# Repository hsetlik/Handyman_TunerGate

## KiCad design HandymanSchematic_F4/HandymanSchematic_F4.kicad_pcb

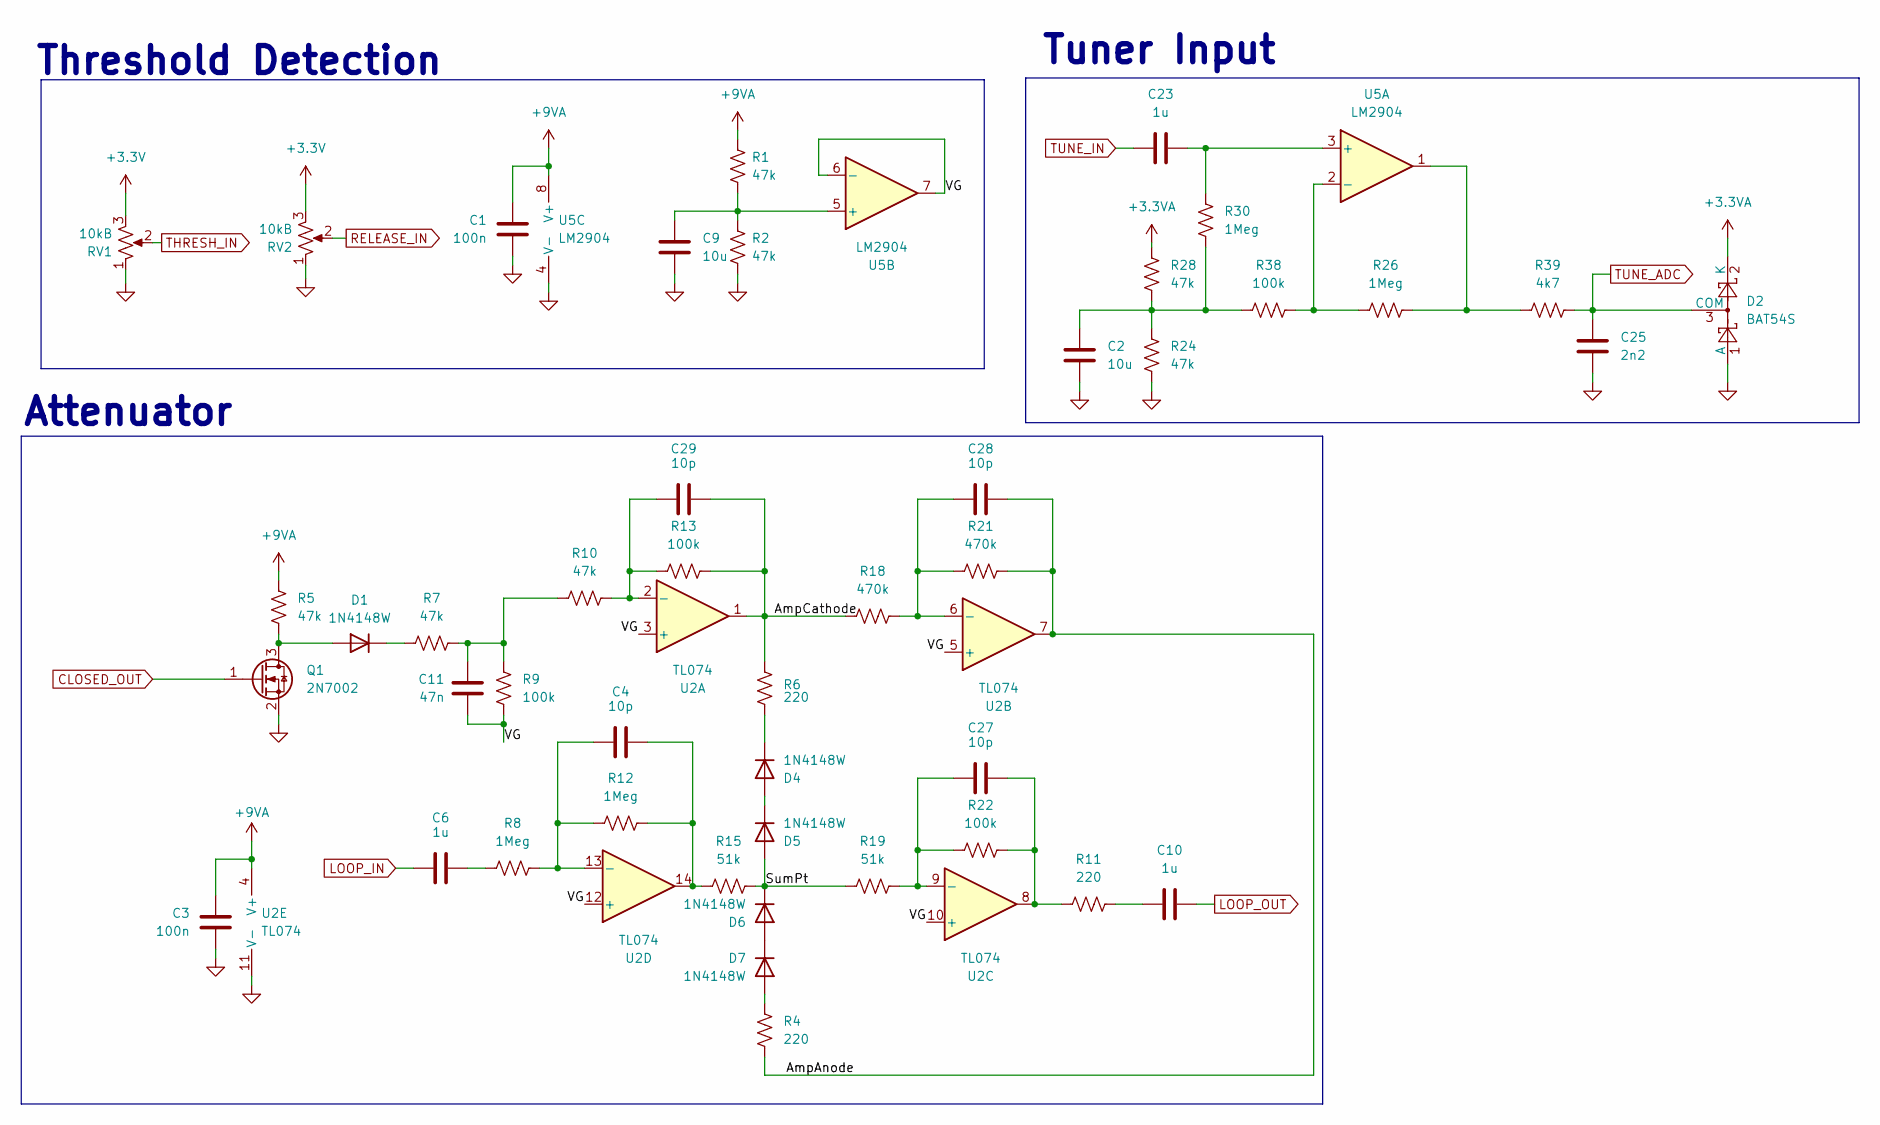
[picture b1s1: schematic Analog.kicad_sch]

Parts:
C1, C3: 100n; C_0805_2012Metric; MPN KGF21BR71H104KT
C2, C9: 10u; C_0805_2012Metric; MPN KGF21BR71H104KT
C4, C27, C28, C29: 10p; C_0805_2012Metric; MPN KGM21AR51E105KU
C6, C10, C23: 1u; C_0805_2012Metric; MPN KGM21AR51E105KU
C11: 47n; C_0805_2012Metric; MPN KGM21NR71H472JM
C25: 2n2; C_0805_2012Metric; MPN KGF21BR71H104KT
D1, D4, D5, D6, D7: 1N4148W; D_SOD-123; MPN 1N4148W-7-F
D2: BAT54S; SOT-23
Q1: 2N7002; SOT-23
R1, R2, R5, R7, R10, R24, R28: 47k; R_0805_2012Metric; MPN RK73B2ATTE473J
R4, R6, R11: 220; R_0805_2012Metric; MPN RC0805FR-10100KL
R8, R12, R26: 1Meg; R_0805_2012Metric; MPN AC0805JR-07470KL
R9, R22: 100k; R_0805_2012Metric; MPN RC0805FR-10100KL
R13, R38: 100k; R_0805_2012Metric; MPN AC0805JR-07470KL
R15, R19: 51k; R_0805_2012Metric; MPN RT0805FRE0751KL
R18, R21: 470k; R_0805_2012Metric; MPN AC0805JR-07470KL
R30: 1Meg; R_0805_2012Metric; MPN RK73B2ATTE473J
R39: 4k7; R_0805_2012Metric; MPN AC0805JR-07470KL
RV1, RV2: 10kB; Potentiometer_Alpha_RD901F-40-00D_Single_Vertical_CircularH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; MPN RV9022NO-PA30B7.0-B10K-000-W3.0
U2: TL074; SOIC-14_3.9x8.7mm_P1.27mm; MPN TL074HIDR
U5: LM2904; SOIC-8_3.9x4.9mm_P1.27mm

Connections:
+3.3V: RV1.3, RV2.3; also elsewhere on the board
+3.3VA: D2.2 (K), R28.1; also elsewhere on the board
+9VA: C1.1, C3.1, R1.1, R5.1, U2.4 (V+), U5.8 (V+); also elsewhere on the board
/Analog/AmpAnode: C28.2, R4.2, R21.2, U2.7
/Analog/AmpCathode: C29.2, R6.1, R13.2, R18.1, U2.1
/Analog/SumPt: D5.2 (A), D6.1 (K), R15.2, R19.1
/Analog/VG: C11.2, R9.2, U2.3 (+), U2.5 (+), U2.10 (+), U2.12 (+), U5.6 (-), U5.7
CLOSED_OUT: Q1.1 (G); also elsewhere on the board
GND: C1.2, C2.2, C3.2, C9.2, C25.2, D2.1 (A), Q1.2 (S), R2.2, R24.2, RV1.1, RV2.1, U2.11 (V-), U5.4 (V-); also elsewhere on the board
LOOP_IN: C6.1; also elsewhere on the board
LOOP_OUT: C10.2; also elsewhere on the board
unnamed: C2.1, R24.1, R28.2, R30.2, R38.1
unnamed: C4.2, R12.2, R15.1, U2.14
unnamed: C6.2, R8.1
unnamed: C10.1, R11.2
unnamed: C11.1, R7.2, R9.1, R10.1
unnamed: C27.2, R11.1, R22.2, U2.8
unnamed: D1.2 (A), Q1.3 (D), R5.2
unnamed: D1.1 (K), R7.1
unnamed: D4.2 (A), D5.1 (K)
unnamed: D4.1 (K), R6.2
unnamed: D6.2 (A), D7.1 (K)
unnamed: D7.2 (A), R4.1
unnamed: R26.2, R39.1, U5.1
unnamed: C29.1, R10.2, R13.1, U2.2 (-)
unnamed: C28.1, R18.2, R21.1, U2.6 (-)
unnamed: C27.1, R19.2, R22.1, U2.9 (-)
unnamed: C4.1, R8.2, R12.1, U2.13 (-)
unnamed: C23.2, R30.1, U5.3 (+)
unnamed: R26.1, R38.2, U5.2 (-)
unnamed: C9.1, R1.2, R2.1, U5.5 (+)
RELEASE_IN: RV2.2; also elsewhere on the board
THRESH_IN: RV1.2; also elsewhere on the board
TUNE_ADC: C25.1, D2.3 (COM), R39.2; also elsewhere on the board
TUNE_IN: C23.1; also elsewhere on the board

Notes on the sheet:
Threshold Detection
Tuner Input
Attenuator

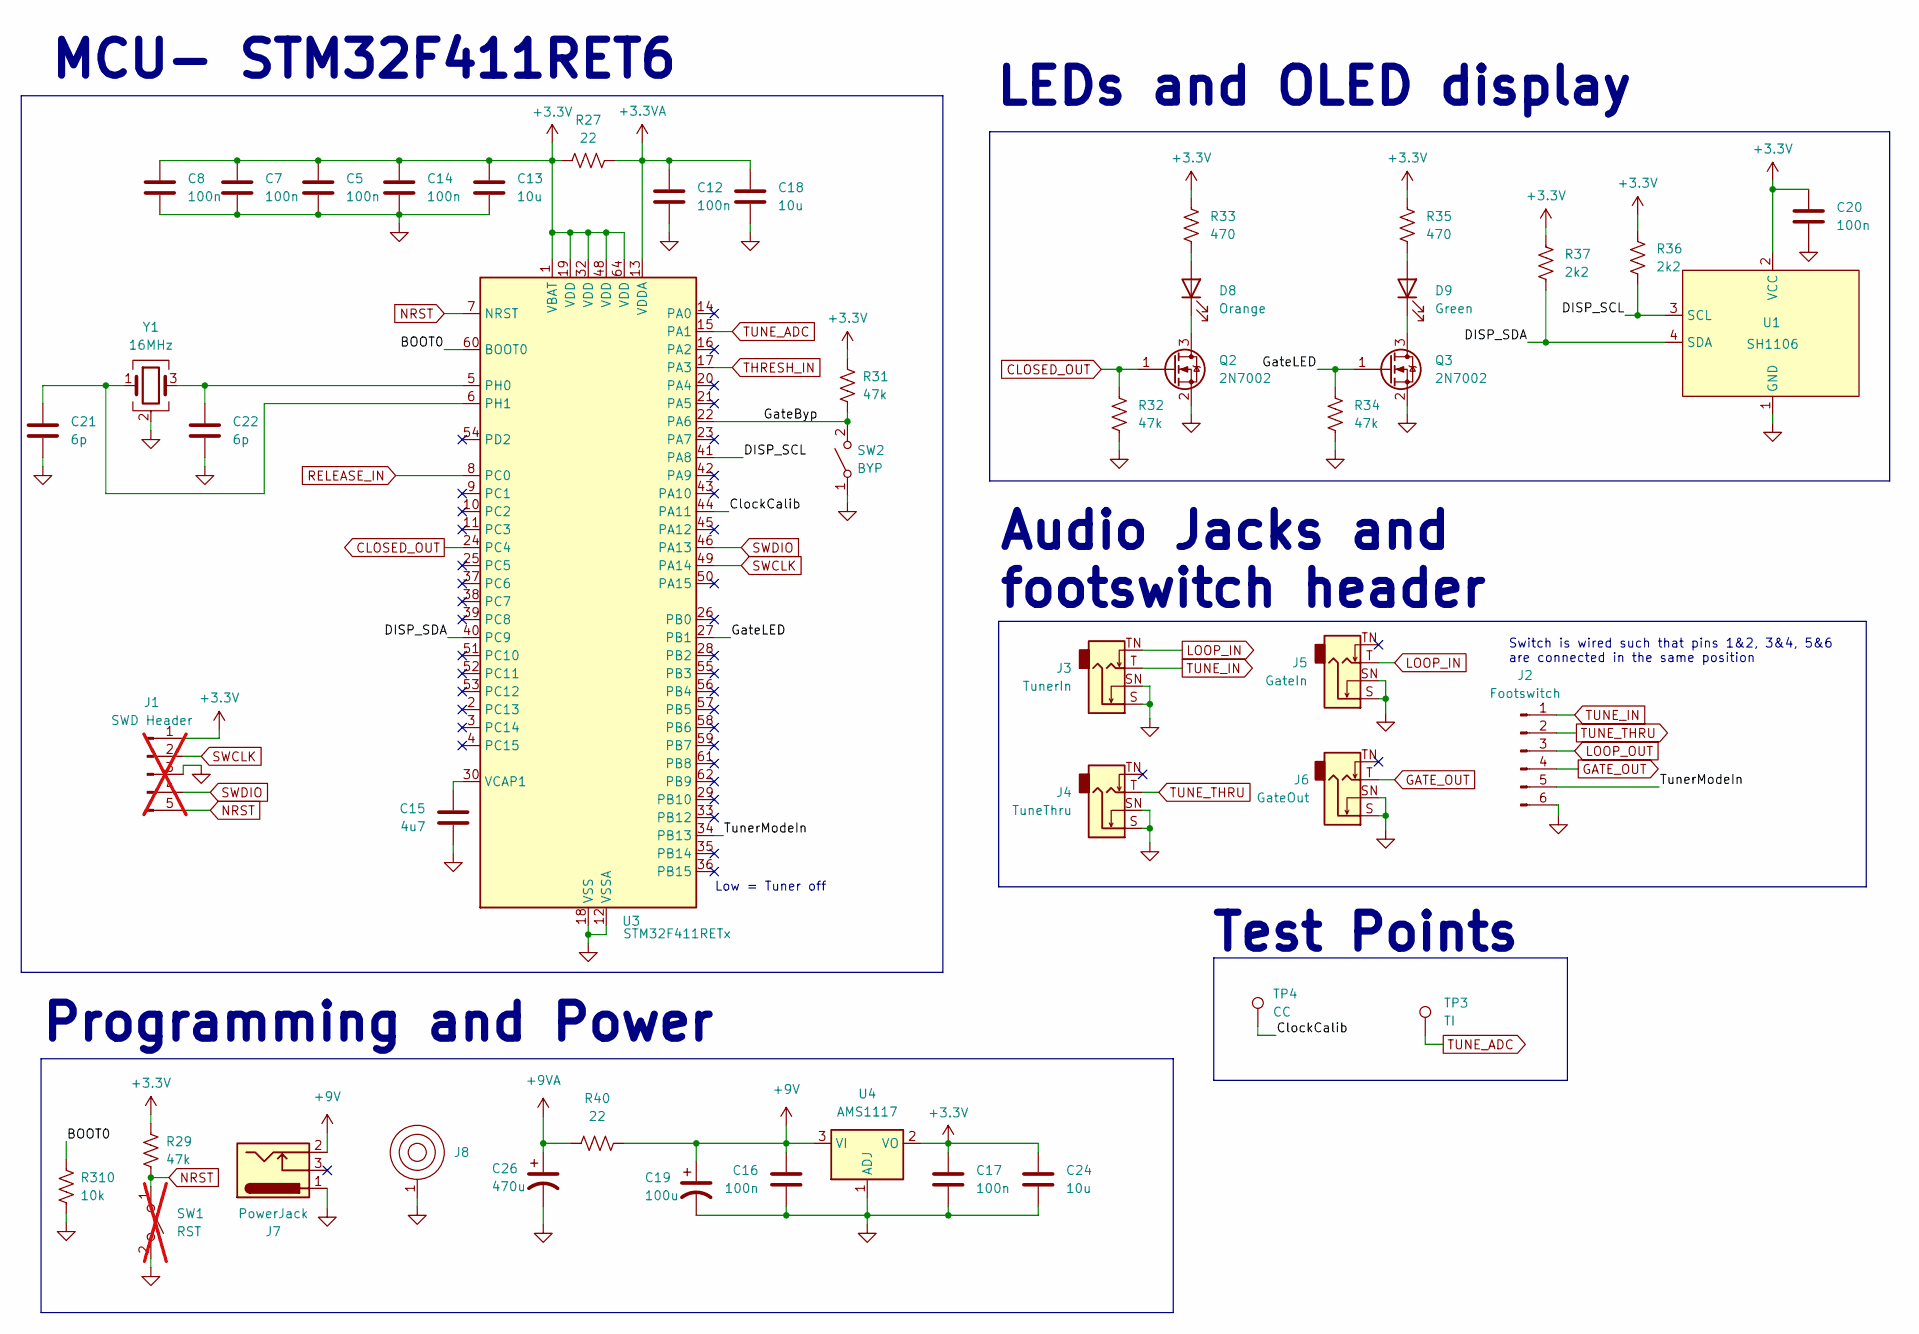
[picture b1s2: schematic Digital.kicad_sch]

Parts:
C5, C7, C8, C12, C14, C16, C17, C20: 100n; C_0805_2012Metric; MPN KGF21BR71H104KT
C13, C18, C24: 10u; C_0805_2012Metric; MPN KGM21AR50J106KU
C15: 4u7; C_0805_2012Metric; MPN CGA4J3X7R1A475K125AB
C19: 100u; CP_Radial_D5.0mm_P2.50mm; MPN ESH107M010AC3AA
C21, C22: 6p; C_0805_2012Metric; MPN 0805N6R0D500CT
C26: 470u; CP_Radial_D6.3mm_P2.50mm; MPN ESH107M010AC3AA
D8: Orange; LED_D3.0mm; MPN LTL-4291N
D9: Green; LED_D3.0mm; MPN LTL-4231N
J1: SWD Header; PinHeader_1x05_P2.54mm_Vertical; not fitted
J2: Footswitch; PinHeader_1x06_P2.54mm_Vertical; MPN SF17N-0302-21R-L-1.1KG-R
J3: TunerIn; Jack_6.35mm_Tayda_PJ664C_Mono_Horizontal; MPN PJ-644C MONO
J4: TuneThru; Jack_6.35mm_Tayda_PJ664C_Mono_Horizontal; MPN PJ-644C MONO
J5: GateIn; Jack_6.35mm_Tayda_PJ664C_Mono_Horizontal; MPN PJ-644C MONO
J6: GateOut; Jack_6.35mm_Tayda_PJ664C_Mono_Horizontal; MPN PJ-644C MONO
J7: PowerJack; BarrelJack_Horizontal; MPN NEB 21 R-C
J8: BatteryContact_Keystone_243
Q2, Q3: 2N7002; SOT-23; MPN 2N7002NXAKR
R27: 22; R_0805_2012Metric; MPN RC0805JR-0722RL
R29, R31, R32, R34: 47k; R_0805_2012Metric; MPN RK73B2ATTE473J
R33, R35: 470; R_0805_2012Metric; MPN RC0805JR-10470RL
R36, R37: 2k2; R_0805_2012Metric; MPN AC0805FR-072K2L
R40: 22; R_0805_2012Metric; MPN RC0805JR-10470RL
R310: 10k; R_0805_2012Metric; MPN AC0805JR-0710KL
SW1: RST; SW_SPST_B3U-1000P; not fitted
SW2: BYP; SW_TH_Tactile_Omron_B3F-102x; MPN TS02-66-90-BK-100-SCR-D
TP3: TI; TestPoint_THTPad_D2.0mm_Drill1.0mm_VAL
TP4: CC; TestPoint_THTPad_D2.0mm_Drill1.0mm_VAL
U1: SH1106; OLED_SH1106_13_OffBoard; MPN SH1106
U3: STM32F411RETx; LQFP-64_10x10mm_P0.5mm; MPN STM32F411RET6TR
U4: AMS1117; SOT-223-3_TabPin2; MPN LD1117S33CTR
Y1: 16MHz; Crystal_SMD_3225-4Pin_3.2x2.5mm; MPN CX3225FB16000B0FZZH1

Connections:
+3.3V: C5.2, C7.2, C8.2, C13.2, C14.2, C17.2, C20.2, C24.2, J1.1, R27.1, R29.1, R31.1, R33.1, R35.1, R36.1, R37.1, U1.2 (VCC), U3.1 (VBAT), U3.19 (VDD), U3.32 (VDD), U3.48 (VDD), U3.64 (VDD), U4.2 (VO); also elsewhere on the board
+3.3VA: C12.2, C18.2, R27.2, U3.13 (VDDA); also elsewhere on the board
+9V: C16.2, C19.1, J7.2, R40.2, U4.3 (VI)
+9VA: C26.1, R40.1; also elsewhere on the board
/Digital/BOOT0: R310.1, U3.60 (BOOT0)
/Digital/ClockCalib: TP4.1 (1_1), U3.44 (PA11)
/Digital/DISP_SCL: R36.2, U1.3 (SCL), U3.41 (PA8)
/Digital/DISP_SDA: R37.2, U1.4 (SDA), U3.40 (PC9)
/Digital/GateByp: R31.2, SW2.2 (B), U3.22 (PA6)
/Digital/GateLED: Q3.1 (G), R34.2, U3.27 (PB1)
/Digital/TunerModeIn: J2.5, U3.34 (PB13)
CLOSED_OUT: Q2.1 (G), R32.2, U3.24 (PC4); also elsewhere on the board
GATE_OUT: J2.4, J6.T
GND: C5.1, C7.1, C8.1, C12.1, C13.1, C14.1, C15.1, C16.1, C17.1, C18.1, C19.2, C20.1, C21.1, C22.1, C24.1, C26.2, J1.3, J2.6, J3.S, J3.SN, J4.S, J4.SN, J5.S, J5.SN, J6.S, J6.SN, J7.1, J8.1, Q2.2 (S), Q3.2 (S), R32.1, R34.1, R310.2, SW1.2 (B), SW2.1 (A), U1.1 (GND), U3.12 (VSSA), U3.18 (VSS), U3.31 (VSS), U3.47 (VSS), U3.63 (VSS), U4.1 (ADJ), Y1.2 (G), Y1.4 (G); also elsewhere on the board
LOOP_IN: J3.TN, J5.T; also elsewhere on the board
LOOP_OUT: J2.3; also elsewhere on the board
NRST: J1.5, R29.2, SW1.1 (A), U3.7 (NRST)
unnamed: D8.2 (A), R33.2
unnamed: D8.1 (K), Q2.3 (D)
unnamed: D9.2 (A), R35.2
unnamed: D9.1 (K), Q3.3 (D)
unnamed: C22.2, U3.5 (PH0), Y1.3
unnamed: C21.2, U3.6 (PH1), Y1.1
unnamed: C15.2, U3.30 (VCAP1)
RELEASE_IN: U3.8 (PC0); also elsewhere on the board
SWCLK: J1.2, U3.49 (PA14)
SWDIO: J1.4, U3.46 (PA13)
THRESH_IN: U3.17 (PA3); also elsewhere on the board
TUNE_ADC: TP3.1 (1_1), U3.15 (PA1); also elsewhere on the board
TUNE_IN: J2.1, J3.T; also elsewhere on the board
TUNE_THRU: J2.2, J4.T

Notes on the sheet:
LEDs and OLED display
Programming and Power
Audio Jacks and footswitch header
Switch is wired such that pins 1&2, 3&4, 5&6 are connected in the same position
Low = Tuner off
MCU- STM32F411RET6
Test Points

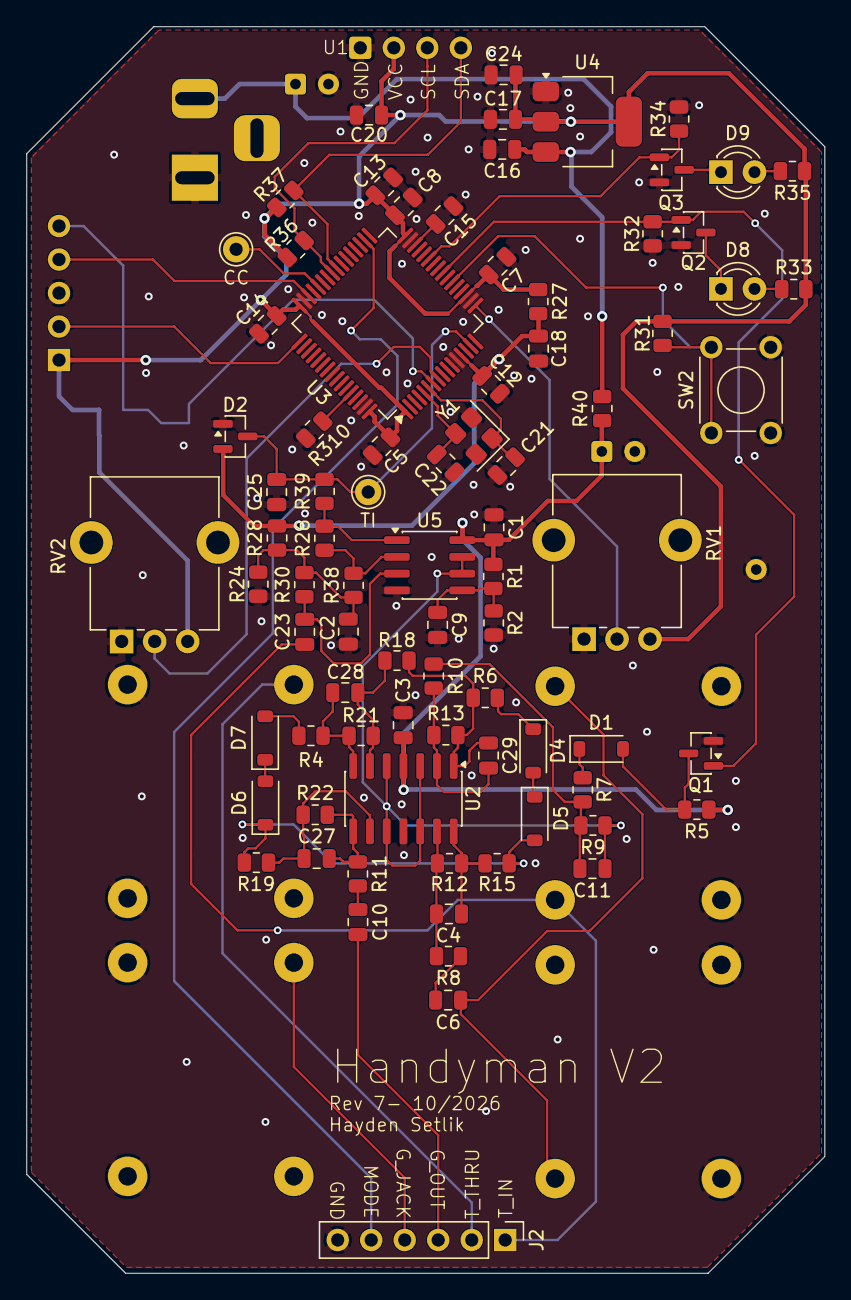
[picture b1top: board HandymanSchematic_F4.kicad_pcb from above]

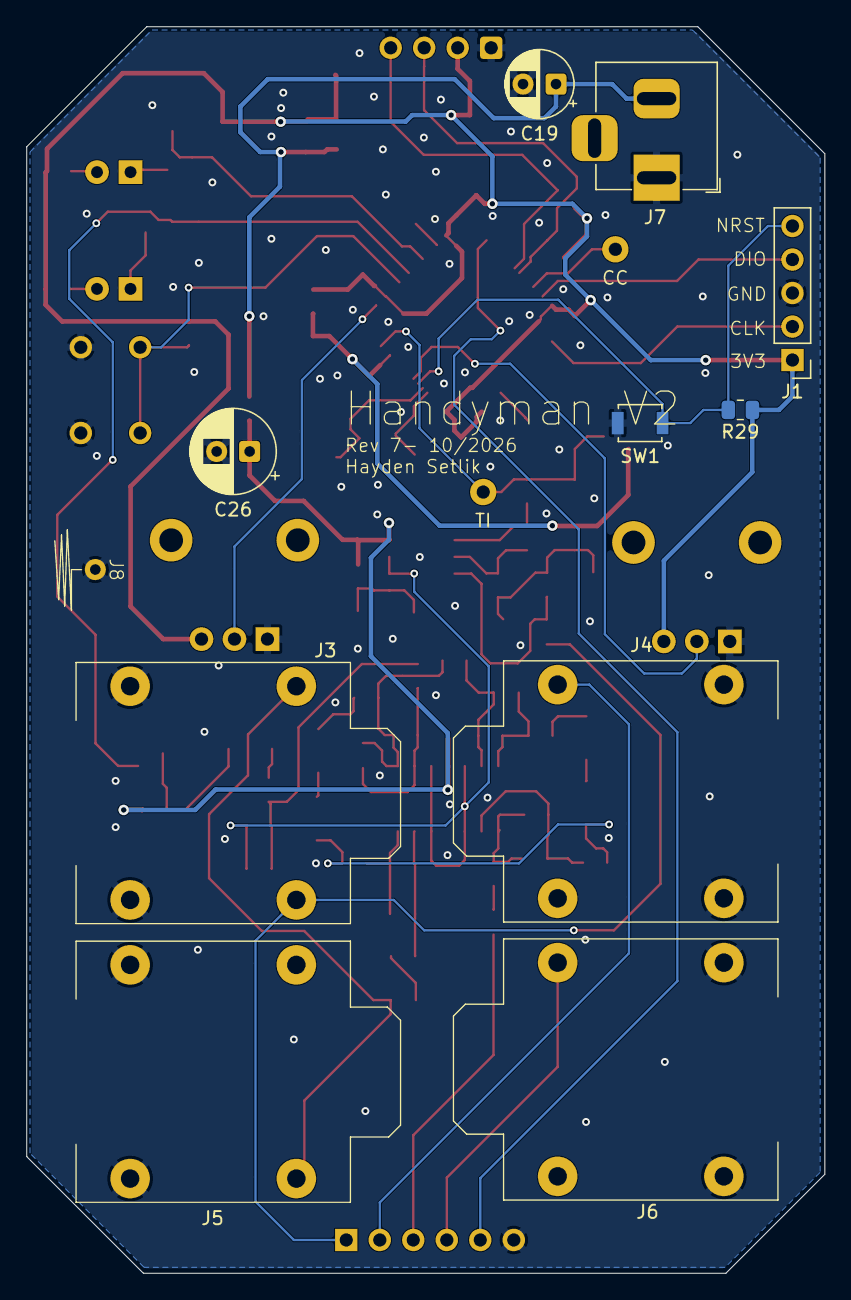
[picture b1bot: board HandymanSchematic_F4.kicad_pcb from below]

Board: 4 copper layers, 60.5 x 94.5 mm, 94 parts (11 on the bottom side), 55 nets.

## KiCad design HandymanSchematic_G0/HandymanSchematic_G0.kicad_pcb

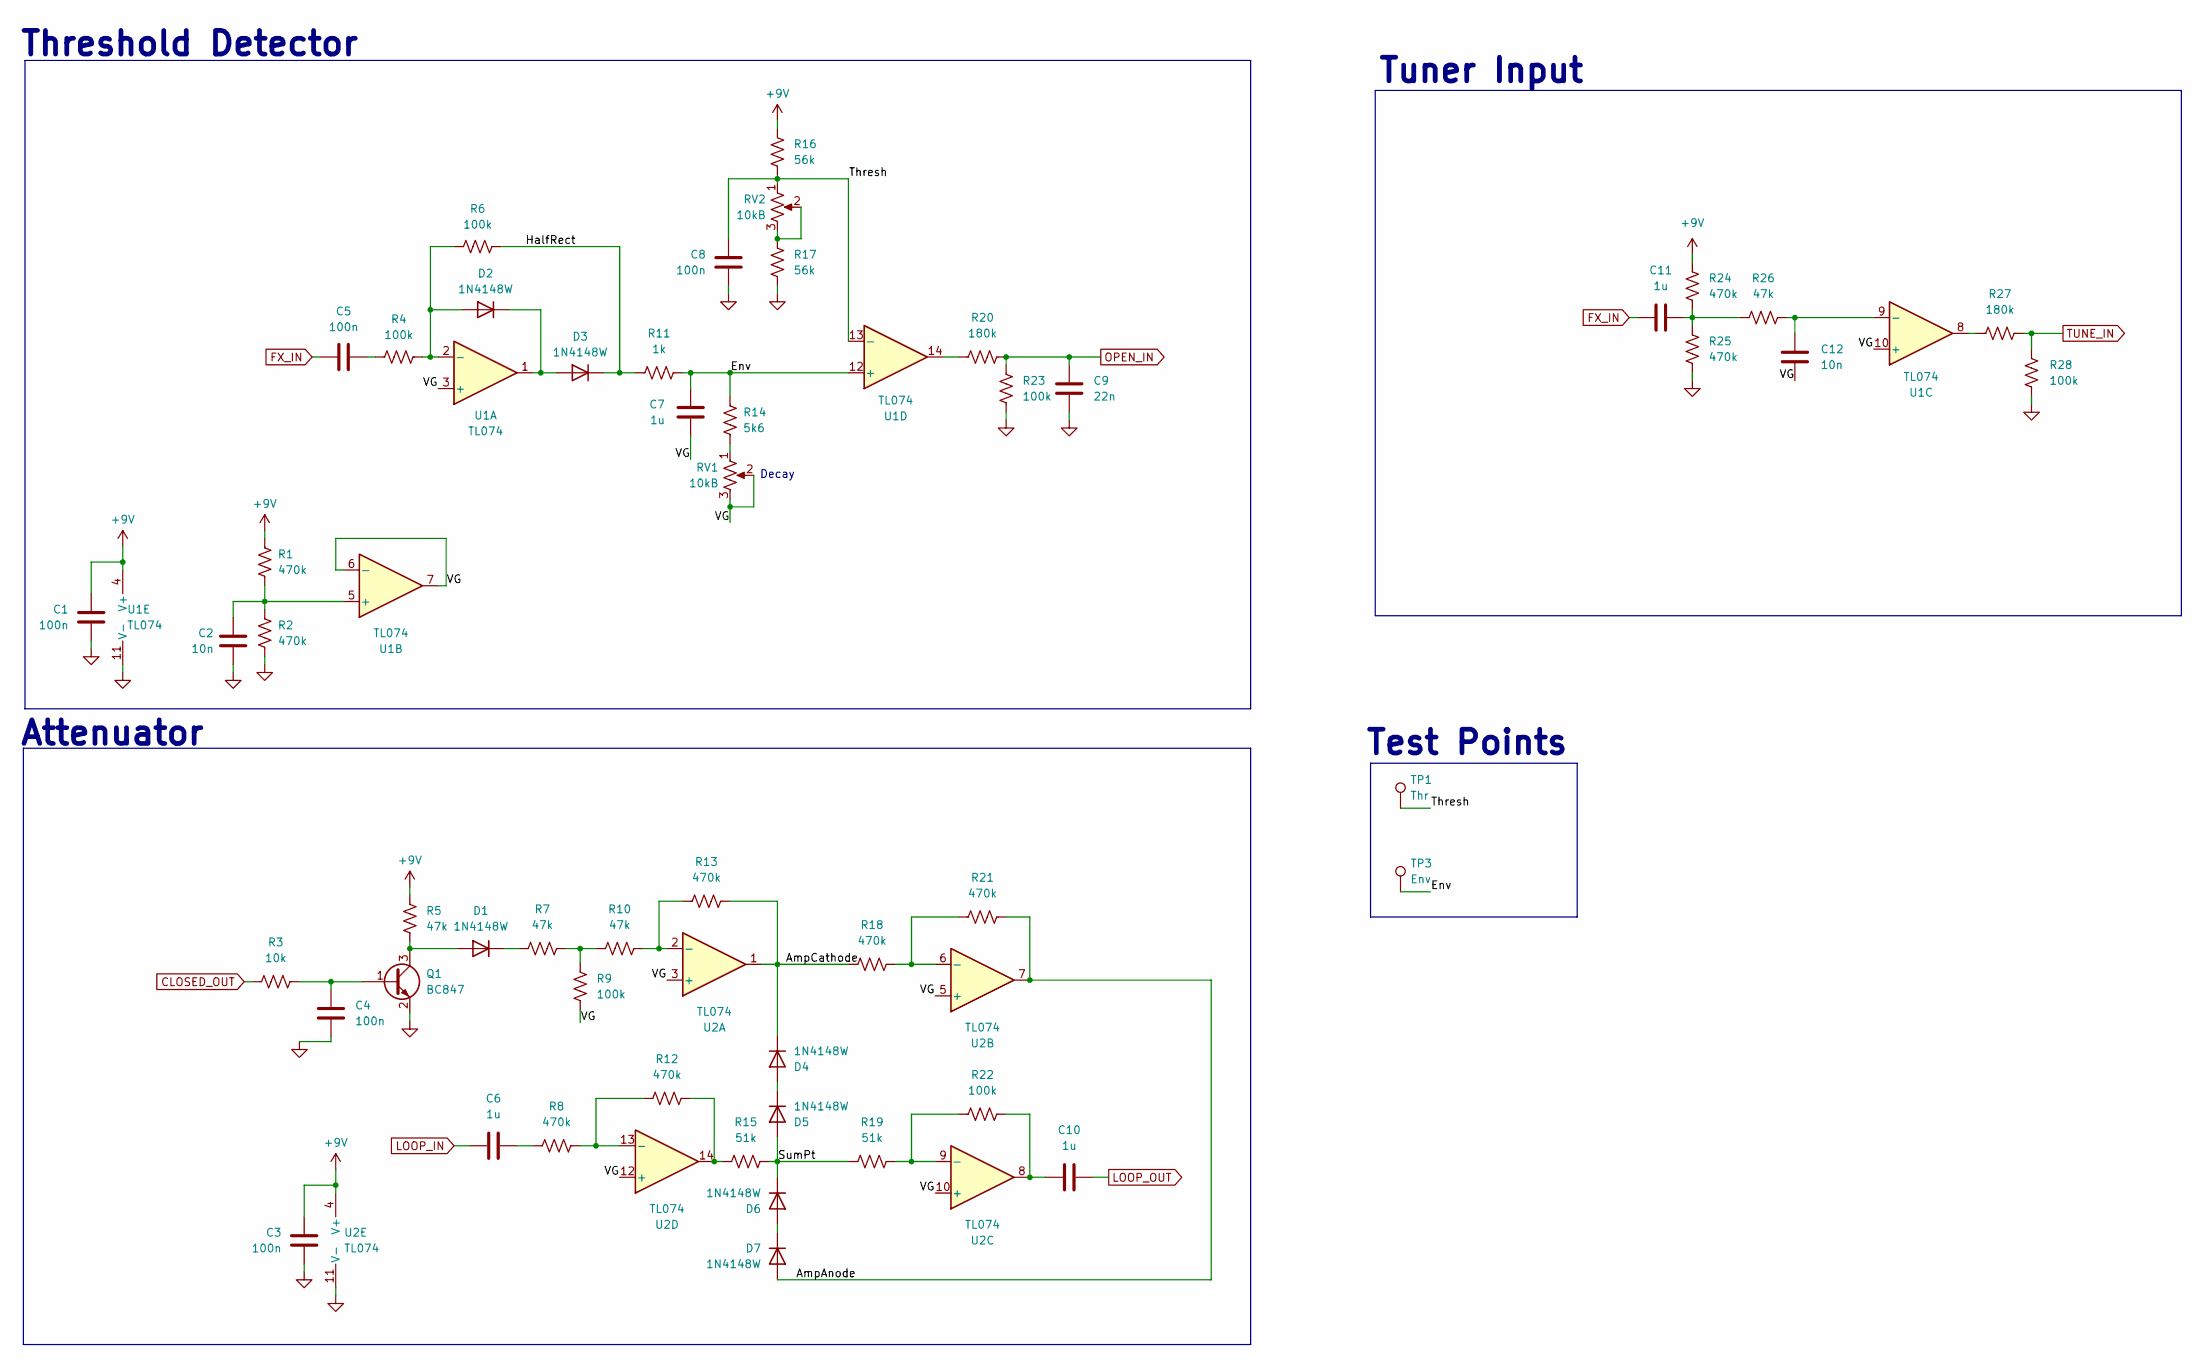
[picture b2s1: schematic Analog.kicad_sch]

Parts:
C1, C3, C4, C5, C8: 100n; C_0805_2012Metric
C2, C12: 10n; C_0805_2012Metric
C6, C7, C10, C11: 1u; C_0805_2012Metric
C9: 22n; C_0805_2012Metric
D1, D2, D3, D4, D5, D6, D7: 1N4148W; D_SOD-123
Q1: BC847; SOT-23
R1, R2, R8, R12, R13, R18, R21, R24, R25: 470k; R_0805_2012Metric
R3: 10k; R_0805_2012Metric
R4, R6, R9, R22, R23, R28: 100k; R_0805_2012Metric
R5, R7, R10, R26: 47k; R_0805_2012Metric
R11: 1k; R_0805_2012Metric
R14: 5k6; R_0805_2012Metric
R15, R19: 51k; R_0805_2012Metric
R16, R17: 56k; R_0805_2012Metric
R20, R27: 180k; R_0805_2012Metric
RV1, RV2: 10kB; Potentiometer_Alpha_RV16AF_42_Single_Long
TP1: Thr; TestPoint_THTPad_D2.0mm_Drill1.0mm_VAL
TP3: Env; TestPoint_THTPad_D2.0mm_Drill1.0mm_VAL
U1, U2: TL074; SOIC-14_3.9x8.7mm_P1.27mm

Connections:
+9V: C1.1, C3.1, R1.1, R5.1, R16.1, R24.2, U1.4 (V+), U2.4 (V+); also elsewhere on the board
/Analog/AmpAnode: D7.2 (A), R21.2, U2.7
/Analog/AmpCathode: D4.1 (K), R13.2, R18.1, U2.1
/Analog/Env: C7.1, R11.2, R14.1, TP3.1, U1.12 (+)
/Analog/HalfRect: D3.1 (K), R6.2, R11.1
/Analog/SumPt: D5.2 (A), D6.1 (K), R15.2, R19.1
/Analog/Thresh: C8.1, R16.2, RV2.1, TP1.1, U1.13 (-)
/Analog/VG: C7.2, C12.1, R9.2, RV1.2, RV1.3, U1.3 (+), U1.6 (-), U1.7, U1.10 (+), U2.3 (+), U2.5 (+), U2.10 (+), U2.12 (+)
CLOSED_OUT: R3.1; also elsewhere on the board
GND: C1.2, C2.2, C3.2, C4.2, C8.2, C9.2, Q1.2 (E), R2.2, R17.2, R23.2, R25.1, R28.1, U1.11 (V-), U2.11 (V-); also elsewhere on the board
LOOP_IN: C6.1; also elsewhere on the board
LOOP_OUT: C10.2; also elsewhere on the board
unnamed: C5.2, R4.1
unnamed: C6.2, R8.1
unnamed: C10.1, R22.2, U2.8
unnamed: C11.2, R24.1, R25.2, R26.1
unnamed: D1.2 (A), Q1.3 (C), R5.2
unnamed: D1.1 (K), R7.1
unnamed: D2.2 (A), R4.2, R6.1, U1.2 (-)
unnamed: D2.1 (K), D3.2 (A), U1.1
unnamed: D4.2 (A), D5.1 (K)
unnamed: D6.2 (A), D7.1 (K)
unnamed: C4.1, Q1.1 (B), R3.2
unnamed: R7.2, R9.1, R10.1
unnamed: R12.2, R15.1, U2.14
unnamed: R14.2, RV1.1
unnamed: R17.1, RV2.2, RV2.3
unnamed: R20.1, U1.14
unnamed: R27.1, U1.8
unnamed: C2.1, R1.2, R2.1, U1.5 (+)
unnamed: C12.2, R26.2, U1.9 (-)
unnamed: R10.2, R13.1, U2.2 (-)
unnamed: R18.2, R21.1, U2.6 (-)
unnamed: R19.2, R22.1, U2.9 (-)
unnamed: R8.2, R12.1, U2.13 (-)
OPEN_IN: C9.1, R20.2, R23.1; also elsewhere on the board
TUNE_IN: R27.2, R28.2; also elsewhere on the board

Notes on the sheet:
Threshold Detector
Tuner Input
Attenuator
Decay
Test Points

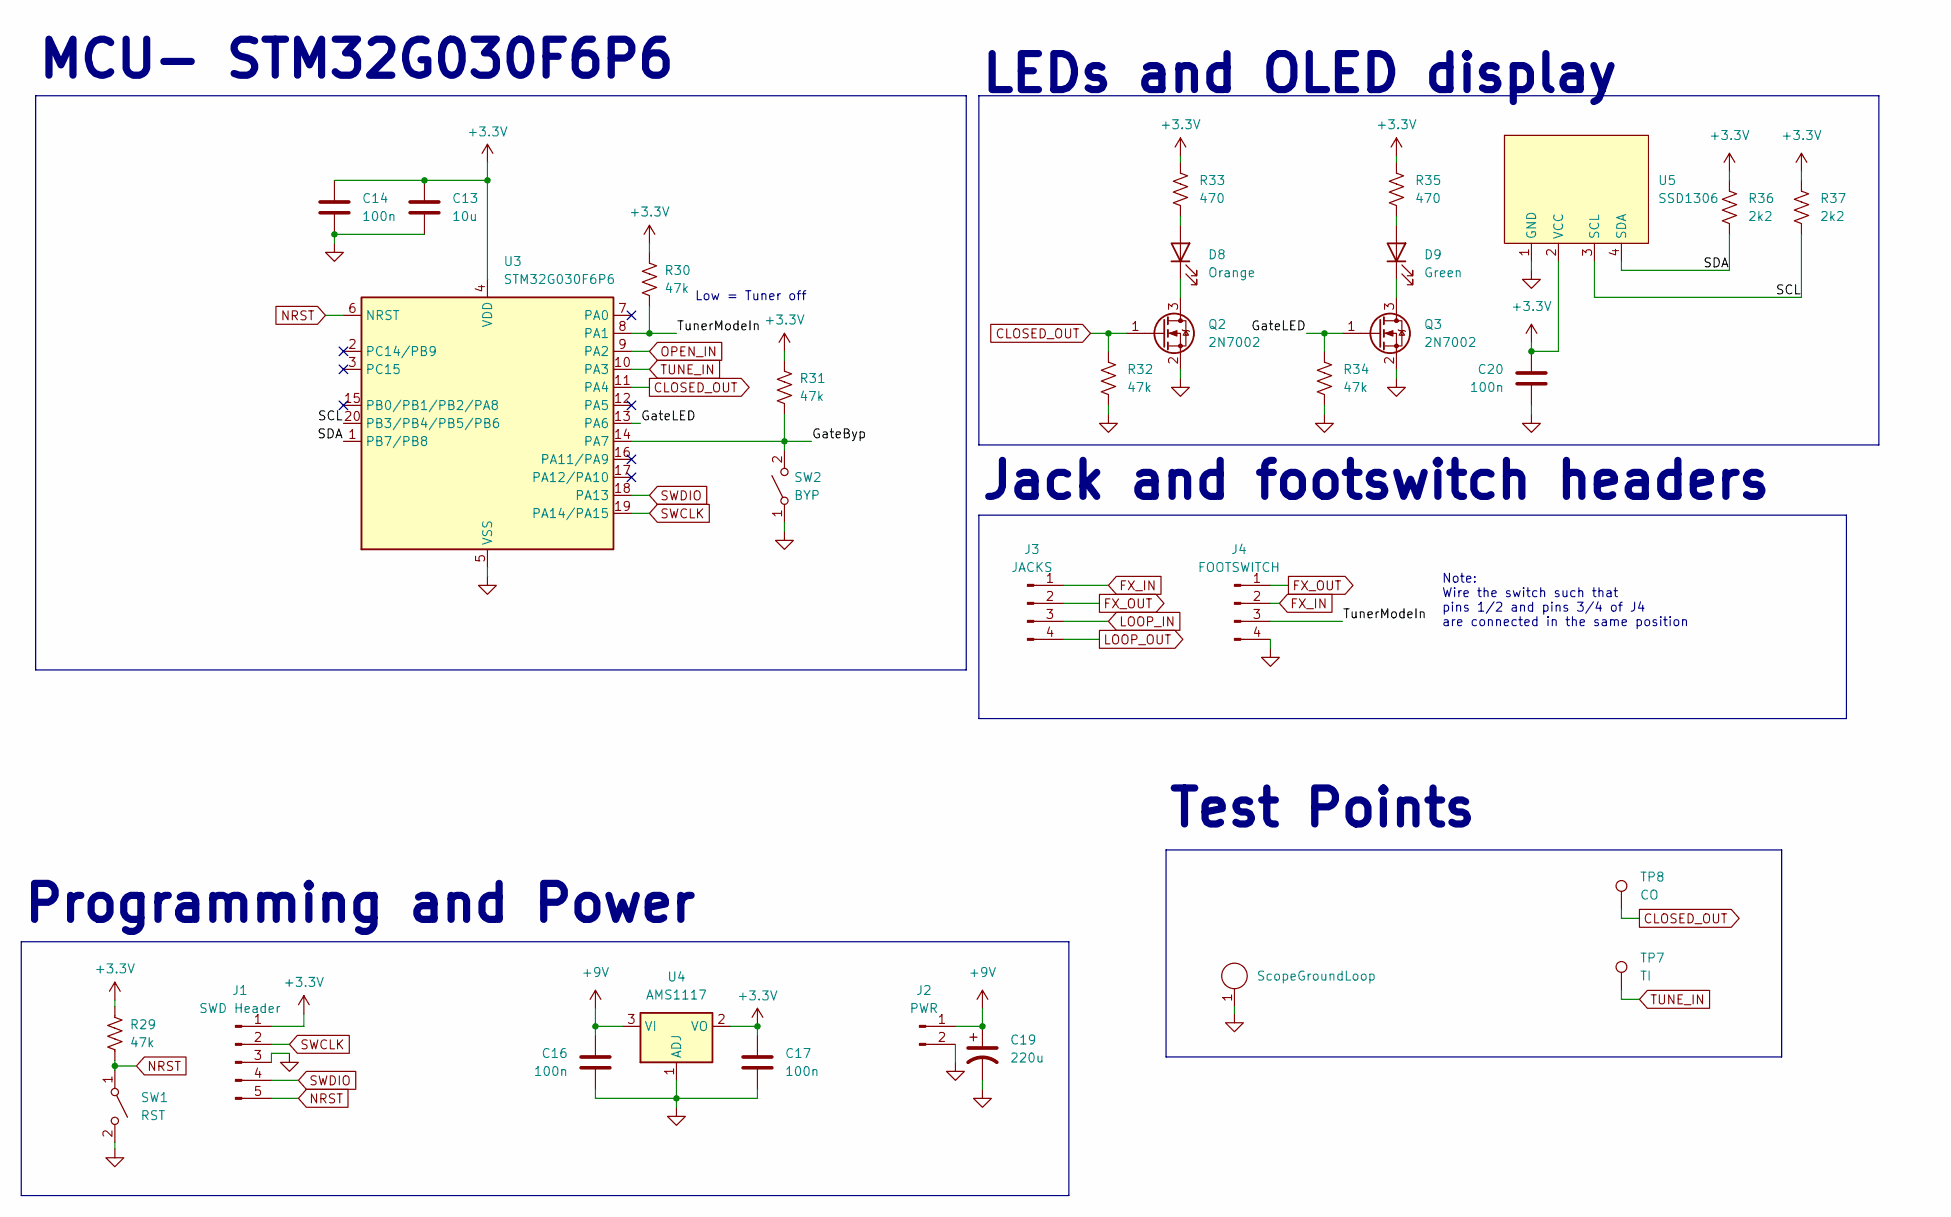
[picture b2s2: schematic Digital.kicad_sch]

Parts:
C13: 10u; C_0805_2012Metric
C14, C16, C17, C20: 100n; C_0805_2012Metric
C19: 220u; CP_Radial_D5.0mm_P2.50mm
D8: Orange; LED_D3.0mm
D9: Green; LED_D3.0mm
J1: SWD Header; PinHeader_1x05_P2.54mm_Vertical
J2: PWR; PinHeader_1x02_P2.54mm_Vertical
J3: JACKS; PinHeader_1x04_P2.54mm_Vertical
J4: FOOTSWITCH; PinHeader_1x04_P2.54mm_Vertical
J5: ScopeGroundLoop; THT_GND_WIRE
Q2, Q3: 2N7002; SOT-23
R29, R30, R31, R32, R34: 47k; R_0805_2012Metric
R33, R35: 470; R_0805_2012Metric
R36, R37: 2k2; R_0805_2012Metric
SW1: RST; SW_SPST_B3U-1000P
SW2: BYP; MiniToggle_SPST
TP7: TI; TestPoint_THTPad_D2.0mm_Drill1.0mm_VAL
TP8: CO; TestPoint_THTPad_D2.0mm_Drill1.0mm_VAL
U3: STM32G030F6P6; TSSOP-20_4.4x6.5mm_P0.65mm
U4: AMS1117; SOT-223-3_TabPin2
U5: SSD1306; SSD1306_OLED_128x64_OffBoard

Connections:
+3.3V: C13.2, C14.2, C17.2, C20.2, J1.1, R29.1, R30.1, R31.1, R33.1, R35.1, R36.1, R37.1, U3.4 (VDD), U4.2 (VO), U5.2 (VCC)
+9V: C16.2, C19.1, J2.1, U4.3 (VI); also elsewhere on the board
/Digital/GateByp: R31.2, SW2.2 (B), U3.14 (PA7)
/Digital/GateLED: Q3.1 (G), R34.2, U3.13 (PA6)
/Digital/SCL: R37.2, U3.20 (PB3/PB4/PB5/PB6), U5.3 (SCL)
/Digital/SDA: R36.2, U3.1 (PB7/PB8), U5.4 (SDA)
/Digital/TunerModeIn: J4.3, R30.2, U3.8 (PA1)
CLOSED_OUT: Q2.1 (G), R32.2, TP8.1, U3.11 (PA4); also elsewhere on the board
GND: C13.1, C14.1, C16.1, C17.1, C19.2, C20.1, J1.3, J2.2, J4.4, J5.1, Q2.2 (S), Q3.2 (S), R32.1, R34.1, SW1.2 (B), SW2.1 (A), U3.5 (VSS), U4.1 (ADJ), U5.1 (GND); also elsewhere on the board
LOOP_IN: J3.3; also elsewhere on the board
LOOP_OUT: J3.4; also elsewhere on the board
NRST: J1.5, R29.2, SW1.1 (A), U3.6 (NRST)
unnamed: D8.2 (A), R33.2
unnamed: D8.1 (K), Q2.3 (D)
unnamed: D9.2 (A), R35.2
unnamed: D9.1 (K), Q3.3 (D)
OPEN_IN: U3.9 (PA2); also elsewhere on the board
SWCLK: J1.2, U3.19 (PA14/PA15)
SWDIO: J1.4, U3.18 (PA13)
TUNE_IN: TP7.1, U3.10 (PA3); also elsewhere on the board

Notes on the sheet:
LEDs and OLED display
Note: Wire the switch such that pins 1/2 and pins 3/4 of J4 are connected in the same position
Jack and footswitch headers
Programming and Power
Low = Tuner off
MCU- STM32G030F6P6
Test Points

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
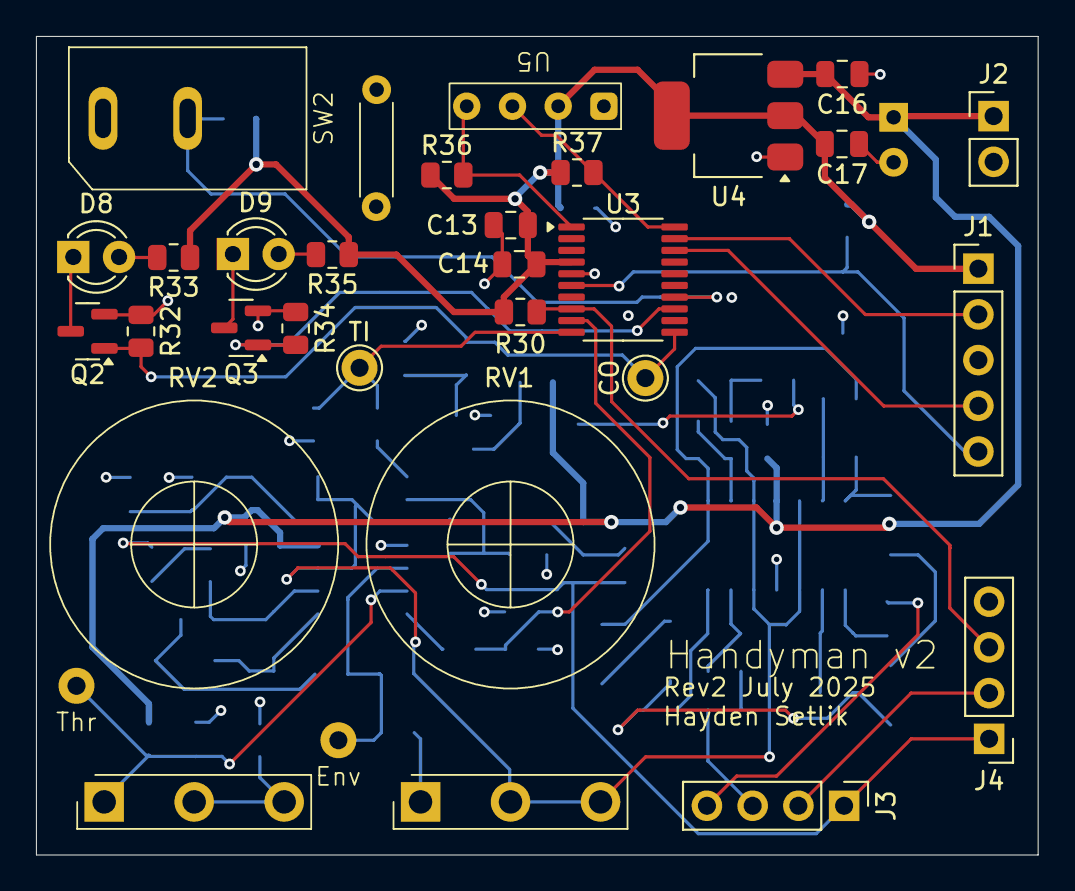
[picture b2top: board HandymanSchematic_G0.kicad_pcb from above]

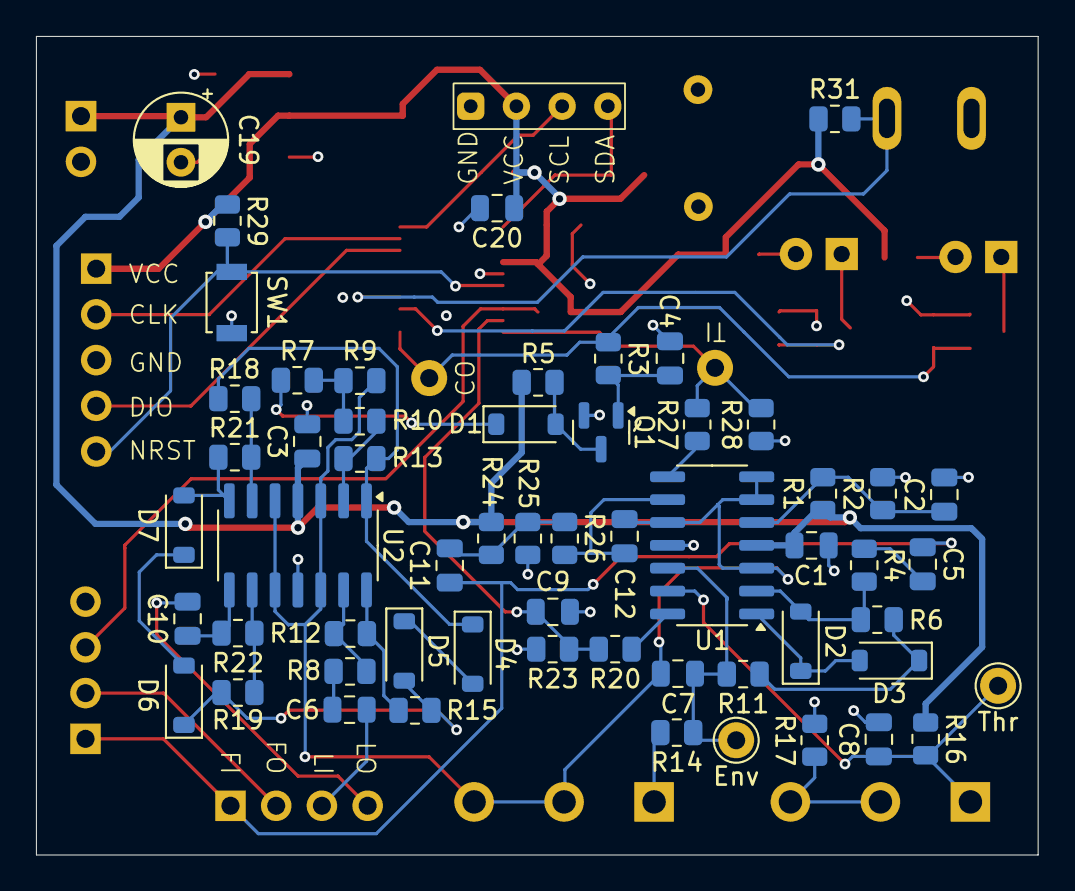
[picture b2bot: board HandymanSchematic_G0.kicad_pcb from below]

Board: 4 copper layers, 55.6 x 45.5 mm, 85 parts (57 on the bottom side), 52 nets.

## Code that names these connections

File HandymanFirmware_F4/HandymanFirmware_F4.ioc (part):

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Mcu.Name=STM32F411R(C-E)Tx
Mcu.Package=LQFP64
Mcu.UserName=STM32F411RETx
PA1.GPIOParameters=GPIO_Label
PA1.GPIO_Label=Audio_IN
PA1.Signal=ADCx_IN1
PA11.GPIOParameters=GPIO_Label
PA11.GPIO_Label=Clock_Calib
PA11.Signal=GPIO_Output
PA13.Mode=Serial_Wire
PA13.Signal=SYS_JTMS-SWDIO
PA14.Mode=Serial_Wire
PA14.Signal=SYS_JTCK-SWCLK
PA3.GPIOParameters=GPIO_Label
PA3.GPIO_Label=Threshold_IN
PA3.Signal=ADCx_IN3
PA6.GPIOParameters=GPIO_Label
PA6.GPIO_Label=UseGate_IN
PA6.Signal=GPIO_Input
PA8.GPIOParameters=GPIO_Label
PA8.GPIO_Label=DISP_SCL
PA8.Mode=I2C
PA8.Signal=I2C3_SCL
PB1.GPIOParameters=GPIO_Label
PB1.GPIO_Label=UseGate_OUT
PB1.Signal=GPIO_Output
PB13.GPIOParameters=GPIO_Label
PB13.GPIO_Label=TunerMode_IN
PB13.Signal=GPIO_Input
PC0.GPIOParameters=GPIO_Label
PC0.GPIO_Label=Release_IN
PC0.Signal=ADCx_IN10
PC4.GPIOParameters=GPIO_Label
PC4.GPIO_Label=GateClosed_OUT
PC4.Signal=GPIO_Output
PC9.GPIOParameters=GPIO_Label
PC9.GPIO_Label=DISP_SDA
PC9.Mode=I2C
PC9.Signal=I2C3_SDA
PH0\ -\ OSC_IN.Mode=HSE-External-Oscillator
PH0\ -\ OSC_IN.Signal=RCC_OSC_IN
PH1\ -\ OSC_OUT.Mode=HSE-External-Oscillator
PH1\ -\ OSC_OUT.Signal=RCC_OSC_OUT
RCC.HSE_VALUE=16000000
RCC.SYSCLKFreq_VALUE=72000000
RCC.SYSCLKSource=RCC_SYSCLKSOURCE_PLLCLK
board=custom

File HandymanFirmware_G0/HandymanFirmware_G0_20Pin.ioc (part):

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Mcu.Name=STM32G030F6Px
Mcu.Package=TSSOP20
Mcu.UserName=STM32G030F6Px
PA1.GPIOParameters=GPIO_Label
PA1.GPIO_Label=TUNER_MODE_IN
PA1.Signal=GPIO_Input
PA13.Mode=Serial_Wire
PA13.Signal=SYS_SWDIO
PA14-BOOT0.Mode=Serial_Wire
PA14-BOOT0.Signal=SYS_SWCLK
PA14-BOOT0__PA15.StandardMode=true
PA2.GPIOParameters=GPIO_Label,GPIO_ModeDefaultEXTI
PA2.GPIO_Label=OPEN_IN
PA2.GPIO_ModeDefaultEXTI=GPIO_MODE_IT_RISING_FALLING
PA2.Signal=GPXTI2
PA3.GPIOParameters=GPIO_Label
PA3.GPIO_Label=TUNE_IN
PA3.Signal=GPXTI3
PA4.GPIOParameters=GPIO_Label
PA4.GPIO_Label=CLOSED_OUT
PA4.Signal=GPIO_Output
PA6.GPIOParameters=GPIO_Label
PA6.GPIO_Label=GATE_LED_OUT
PA6.Signal=GPIO_Output
PA7.GPIOParameters=GPIO_Label
PA7.GPIO_Label=GATE_BYP_IN
PA7.Signal=GPIO_Input
PB0__PB1__PB2__PA8.StandardMode=true
PB3__PB4__PB5__PB6.StandardMode=true
PB6.Mode=I2C
PB6.Signal=I2C1_SCL
PB7.Mode=I2C
PB7.Signal=I2C1_SDA
PB7__PB8.StandardMode=true
PC14-OSC32_IN\ (PC14)__PB9.StandardMode=true
RCC.HSE_VALUE=8000000
RCC.SYSCLKFreq_VALUE=64000000
RCC.SYSCLKSource=RCC_SYSCLKSOURCE_PLLCLK
board=custom
